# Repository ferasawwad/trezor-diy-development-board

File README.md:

# Trezor Diy Development Board
This is hardware project designed to work with <a href="http://www.waveshare.com/wiki/Core205R">Core205R</a> development board with custom arm STM32F205RGT6.
If anyone needs custom board can be ordered from <a href="http://www.waveshare.com/">Waveshare</a>.

Bootloader & firmware https://github.com/trezor/trezor-mcu

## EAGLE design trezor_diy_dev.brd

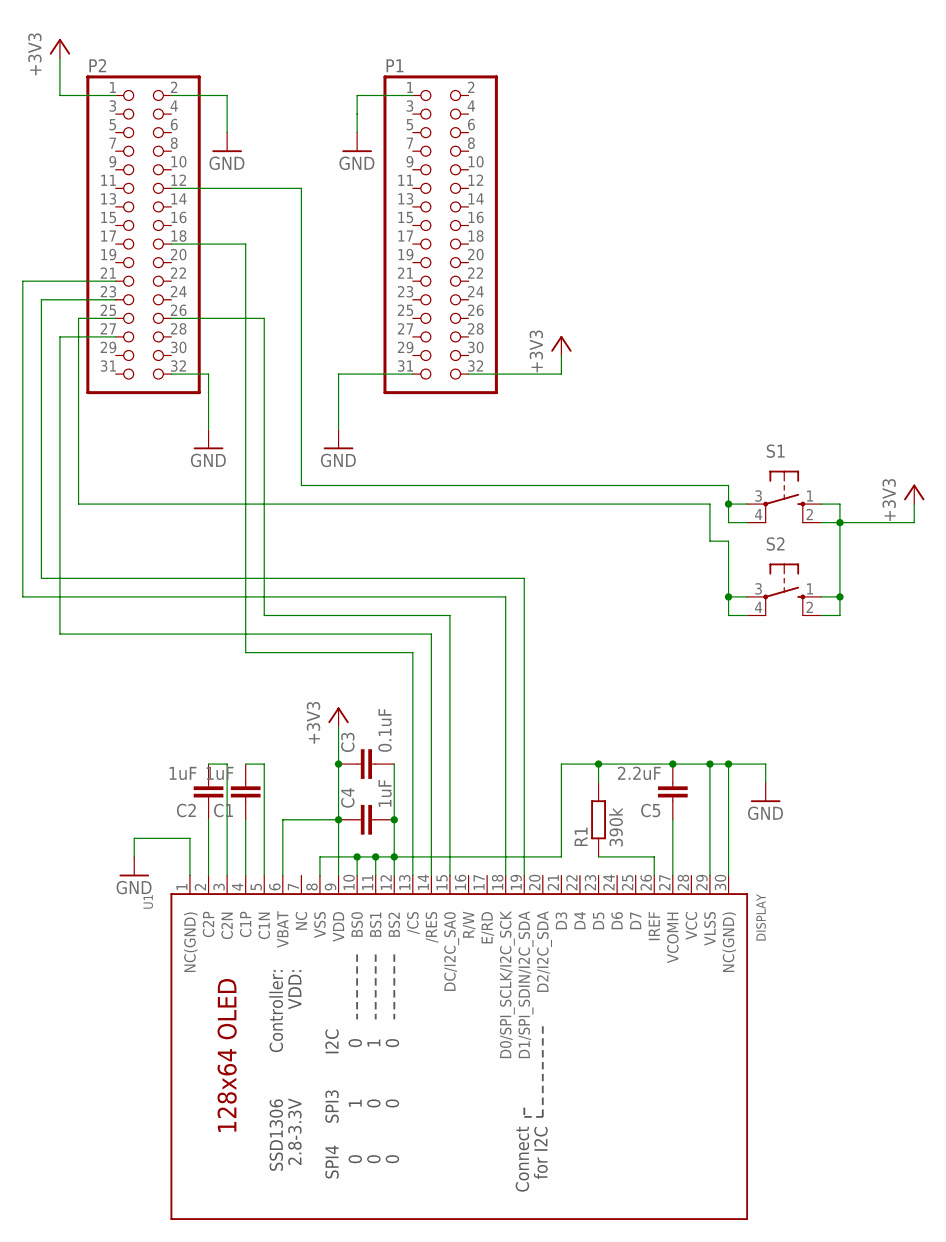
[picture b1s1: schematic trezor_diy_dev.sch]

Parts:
C1, C2, C4: 1uF; C5B2.5
C3: 0.1uF; C5B2.5
C5: 2.2uF; C5B2.5
P1, P2: PINHD-2X16; 2X16
R1: 390k; 0309/10
S1, S2: 10-XX; B3F-10XX
U1: DISPLAY; UG-2864HSWEG01_0.96IN_WRAPAROUND

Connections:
3V3: U1.28 (VCC)
+3V3: C3.1, C4.1, P1.32, P2.1, S1.1 (S), S1.2 (S1), S2.1 (S), S2.2 (S1), U1.6 (VBAT), U1.9 (VDD)
GND: C3.2, C4.2, C5.2, P1.1, P1.31, P2.2, P2.32, R1.2, U1.1 (NC(GND)), U1.8 (VSS), U1.10 (BS0), U1.11 (BS1), U1.12 (BS2), U1.29 (VLSS), U1.30 (NC(GND))
unnamed: C2.2, U1.3 (C2N)
unnamed: P2.25, S2.3, S2.4 (P1)
unnamed: P2.12, S1.3, S1.4 (P1)
unnamed: P2.26, U1.15 (DC/I2C_SA0)
unnamed: P2.21, U1.18 (D0/SPI_SCLK/I2C_SCK)
unnamed: C5.1, U1.27 (VCOMH)
unnamed: P2.18, U1.13 (/CS)
unnamed: P2.27, U1.14 (/RES)
unnamed: R1.1, U1.26 (IREF)
unnamed: C2.1, U1.2 (C2P)
unnamed: C1.1, U1.4 (C1P)
unnamed: C1.2, U1.5 (C1N)
unnamed: P2.23, U1.19 (D1/SPI_SDIN/I2C_SDA)

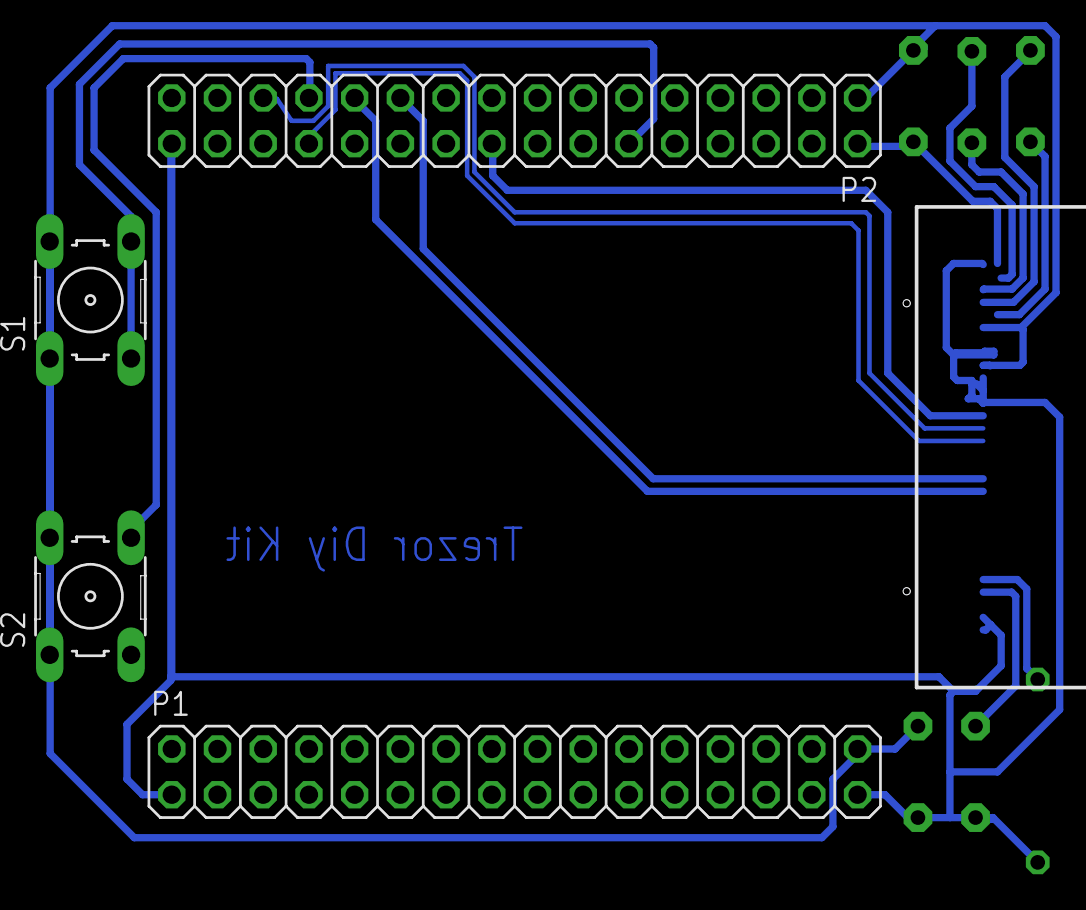
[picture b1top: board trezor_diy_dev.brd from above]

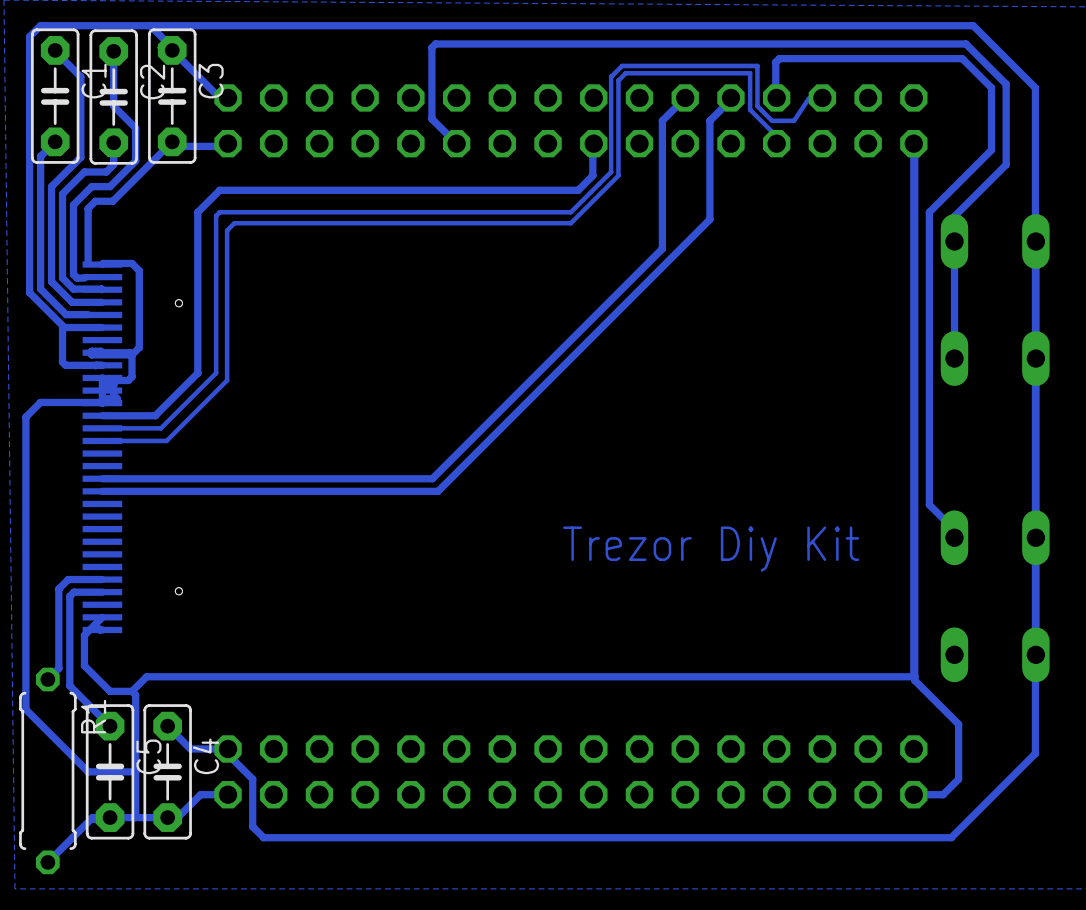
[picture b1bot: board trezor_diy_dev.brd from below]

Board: 2 copper layers, 11 parts (6 on the bottom side), 15 nets.

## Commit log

2018-04-29 Create LICENSE

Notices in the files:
parts and their libraries:
microbuilder: This work is placed in the public domain, and may be freely used for commercial and non-commercial work with the following conditions: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
